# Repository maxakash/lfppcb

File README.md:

# LFP-8: 40-cell LiFePO4 33140 charger / discharger / IR tester

An open hardware tester for LiFePO4 32140/33140 cells. One **LFP-8 board**
handles **8 cells**. Five boards, JLCPCB's minimum order, test **40 cells at
once**. Each channel can

* **charge** with constant current then constant voltage: ≈ 1.0 A, CV 3.58 V,
  hardware OV latch at 3.82 V
* **discharge** at ≈ 1.07 A, with a hardware under-voltage backstop at 2.22 V
* measure **capacity** (coulomb counting, mAh/mWh) and **internal resistance**
  (pulse method, R_ohmic at 10 ms and DC-IR at 1 s) through true **4-wire
  Kelvin** connections
* read a 10 k **NTC** on every cell

Every board reports over Wi-Fi: a web dashboard and a JSON API served by its
ESP32-C3. The boards find each other, so any one of them shows all 40 cells.

| | |
|---|---|
|  |  |
| LFP-8 PCB (216 × 146 mm, 2 layers, JLCPCB assembly) | 3D-printed 8-cell module + board stand (Ender 3 S1 Pro) |

## Repository map

| Path | What |
|---|---|
| [`docs/DESIGN.md`](docs/DESIGN.md) | Architecture, circuit description, design numbers |
| [`docs/INTERFACE.md`](docs/INTERFACE.md) | Hardware ⇄ firmware contract: GPIO map, shift-register bits, thresholds, measurement formulas |
| [`docs/TEST_REPORT.md`](docs/TEST_REPORT.md) | Results of every simulation, adversarial and board-level test |
| [`docs/ORDERING_AND_ASSEMBLY.md`](docs/ORDERING_AND_ASSEMBLY.md) | How to order from JLCPCB, hand-solder parts, wiring, bring-up |
| `hardware/gen/` | **Single source of truth**: the netlist DSL (`lfp8_circuit.py`) and the generators for schematic, PCB, routing, checks and fab files |
| `hardware/kicad/` | Generated KiCad 7 project (schematic, PCB, project library) |
| `hardware/fab/` | Gerbers, drill, JLCPCB BOM + CPL, DRC report, check report |
| `sim/` | ngspice models, benches and the pytest suite (functional, adversarial, Monte Carlo, loop stability) |
| `firmware/` | ESP32-C3 Arduino firmware, web UI, REST API, IR calculator, host tests and simulator |
| `mechanical/` | OpenSCAD holder (4-cell cradles, board stand), STLs, printability checks |

## Quick start

1. **Order PCBs**: upload `hardware/fab/lfp8_gerbers.zip`, then
   `lfp8_bom_jlcpcb.csv` and `lfp8_cpl_jlcpcb.csv` for assembly. Details in
   [ORDERING_AND_ASSEMBLY.md](docs/ORDERING_AND_ASSEMBLY.md).
2. **Print the holders**: `mechanical/stl/`, 10 cradles + 5 board stands, PETG,
   no supports.
3. **Flash the firmware** through the J3 USB header:
   `make -C firmware build upload`, or open `firmware/lfp8` in the Arduino IDE
   with the ESP32 core, board *ESP32C3 Dev Module*, partition scheme
   *Minimal SPIFFS*.
4. **Power**: 5.20 V, ≥ 10 A per board. Join the board's Wi-Fi AP `LFP8-<id>` (password `lfp8admin`)
   and open `http://192.168.4.1`, or configure your Wi-Fi and use
   `http://lfp8-<id>.local`.

## Safety features (hardware, independent of firmware)

| Feature | Behaviour |
|---|---|
| CV limit | Kelvin-sensed 3.576 V (3.51–3.62 V worst case); firmware also stops at 3.60 V |
| OV latch | 3.82 V: cell isolated + charger drive killed until the cell is removed or SAFE_EN cycles |
| UV backstop | discharge stops at 2.22 V under load even if firmware hangs |
| Charge/discharge interlock | the charger is forced off while the load is on |
| Reverse cell | detected in < 50 µs; cell isolated (0.1 mA residual) whether the board is powered or not |
| Back-to-back isolation FETs | an unpowered board does not drain or back-feed the cells (81 µA residual) |
| Watchdog | a stuck or too-slow firmware loop (< 100 Hz heartbeat) shuts every channel down in 23–33 ms |
| Rail UV / OV | 4.48 V / 5.49 V |
| Board over-temperature | 70–95 °C → all channels off |
| E-STOP button | all channels off in 126 µs |
| PTC fuse per channel | 2 A hold; a board-side short trips in 0.22 s |
| TVS + reverse crowbar on the 5 V input | |

## Running the tests

```bash
./run_all_tests.sh          # ngspice suite, netlist + DRC checks, firmware tests, holder checks
QUICK=1 ./run_all_tests.sh  # shorter Monte Carlo
```

Regenerate the hardware from the DSL with `make -C hardware` (KiCad 7,
Freerouting 2.x and Java are required for routing).

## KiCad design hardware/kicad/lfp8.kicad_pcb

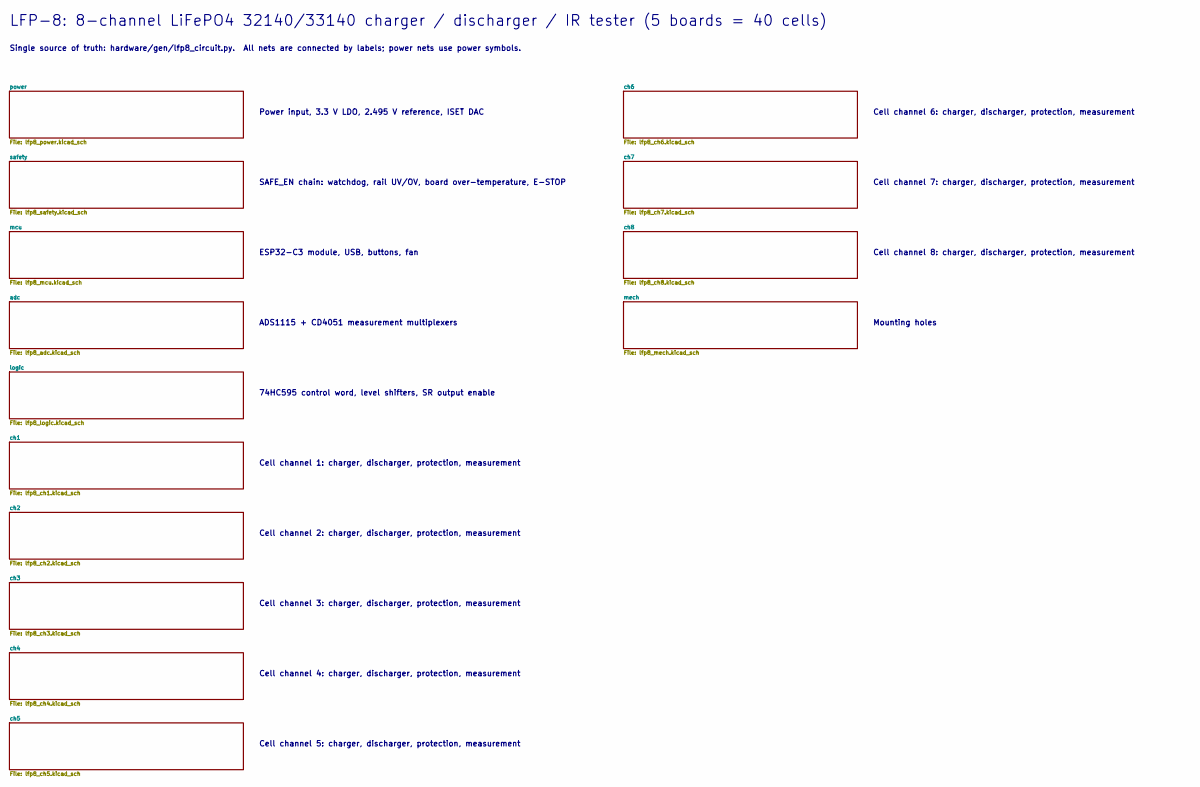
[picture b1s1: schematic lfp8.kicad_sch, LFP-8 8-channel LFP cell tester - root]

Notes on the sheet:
Power input, 3.3 V LDO, 2.495 V reference, ISET DAC
SAFE_EN chain: watchdog, rail UV/OV, board over-temperature, E-STOP
ESP32-C3 module, USB, buttons, fan
ADS1115 + CD4051 measurement multiplexers
74HC595 control word, level shifters, SR output enable
Cell channel 1: charger, discharger, protection, measurement
Cell channel 2: charger, discharger, protection, measurement
Cell channel 3: charger, discharger, protection, measurement
Cell channel 4: charger, discharger, protection, measurement
Cell channel 5: charger, discharger, protection, measurement
Cell channel 6: charger, discharger, protection, measurement
Cell channel 7: charger, discharger, protection, measurement
Cell channel 8: charger, discharger, protection, measurement
Mounting holes
LFP-8: 8-channel LiFePO4 32140/33140 charger / discharger / IR tester (5 boards = 40 cells)
Single source of truth: hardware/gen/lfp8_circuit.py. All nets are connected by labels; power nets use power symbols.

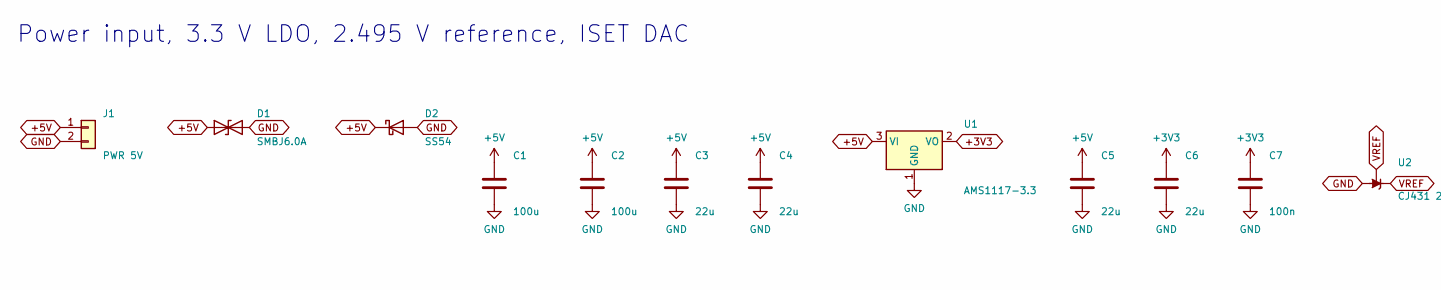
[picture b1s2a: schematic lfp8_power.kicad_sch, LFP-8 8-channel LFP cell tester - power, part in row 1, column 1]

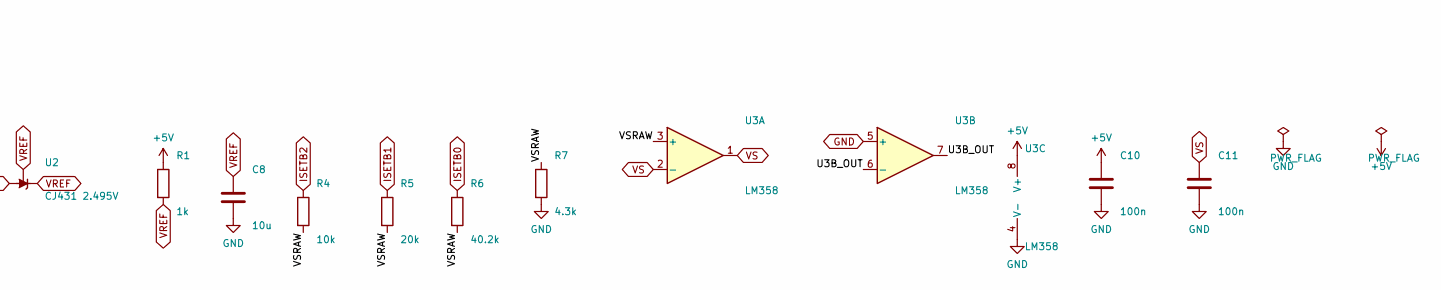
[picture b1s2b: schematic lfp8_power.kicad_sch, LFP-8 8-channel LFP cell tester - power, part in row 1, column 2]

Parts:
C1, C2: 100u; C_1206_3216Metric; LCSC C15008
C3, C4: 22u; C_1206_3216Metric; LCSC C12891
C5, C6: 22u; C_0805_2012Metric; LCSC C45783
C7, C10, C11: 100n; C_0603_1608Metric; LCSC C14663
C8: 10u; C_0805_2012Metric; LCSC C15850
D1: SMBJ6.0A; D_SMB; MPN SMBJ6.0A; LCSC C19077560
D2: SS54; D_SMA; MPN SS54; LCSC C22452
J1: PWR 5V; TerminalBlock_bornier-2_P5.08mm; MPN KF301-5.0-2P / 2-pin 5.08 mm 16 A termi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; JLC Hand
R1: 1k; R_0603_1608Metric; LCSC C21190
R4: 10k; R_0603_1608Metric; LCSC C25804
R5: 20k; R_0603_1608Metric; LCSC C4184
R6: 40.2k; R_0603_1608Metric; LCSC C12447
R7: 4.3k; R_0603_1608Metric; LCSC C23159
U1: AMS1117-3.3; SOT-223-3_TabPin2; MPN AMS1117-3.3; LCSC C6186
U2: CJ431 2.495V; SOT-23; MPN CJ431; LCSC C3113
U3: LM358; SOIC-8_3.9x4.9mm_P1.27mm; MPN LM358DR2G; LCSC C7950

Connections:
+3V3: C6.1, C7.1, U1.2 (VO); also elsewhere on the board
+5V: C1.1, C2.1, C3.1, C4.1, C5.1, C10.1, D1.1 (A1), D2.1 (K), J1.1, R1.1, U1.3 (VI), U3.8 (V+); also elsewhere on the board
/power/U3B_OUT: U3.6 (-), U3.7
/power/VSRAW: R4.2, R5.2, R6.2, R7.1, U3.3 (+)
GND: C1.2, C2.2, C3.2, C4.2, C5.2, C6.2, C7.2, C8.2, C10.2, C11.2, D1.2 (A2), D2.2 (A), J1.2, R7.2, U1.1 (GND), U2.3 (A), U3.4 (V-), U3.5 (+); also elsewhere on the board
ISETB0: R6.1; also elsewhere on the board
ISETB1: R5.1; also elsewhere on the board
ISETB2: R4.1; also elsewhere on the board
VREF: C8.1, R1.2, U2.1 (K), U2.2 (REF); also elsewhere on the board
VS: C11.1, U3.1, U3.2 (-); also elsewhere on the board

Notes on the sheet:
Power input, 3.3 V LDO, 2.495 V reference, ISET DAC

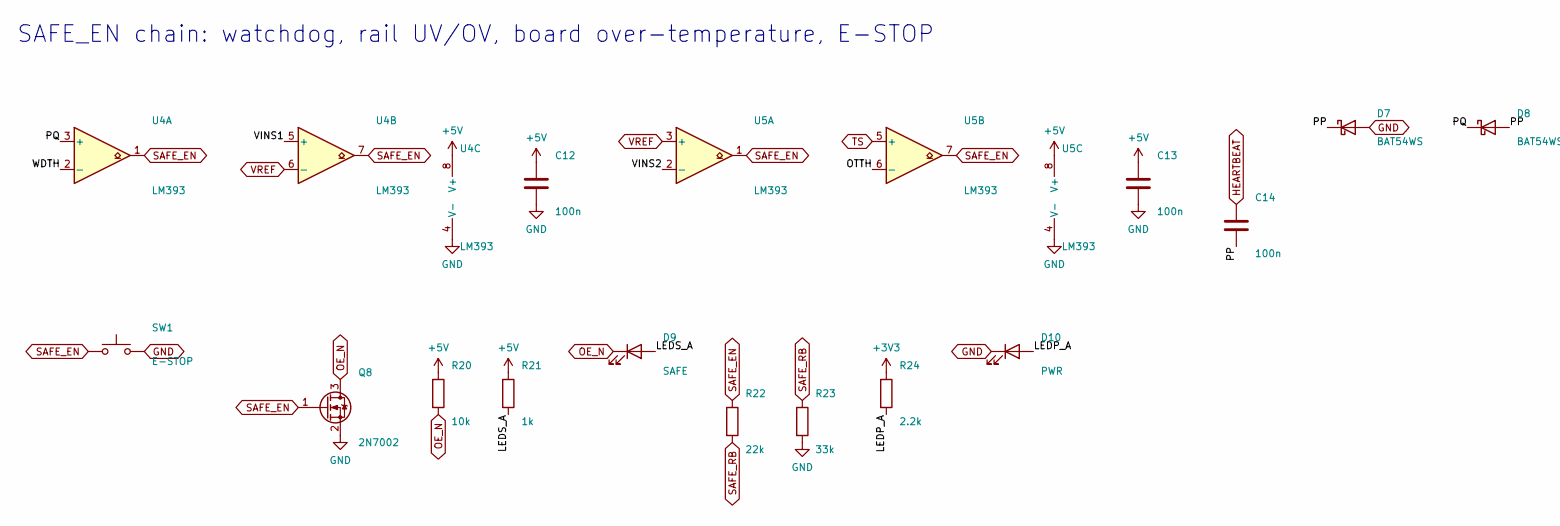
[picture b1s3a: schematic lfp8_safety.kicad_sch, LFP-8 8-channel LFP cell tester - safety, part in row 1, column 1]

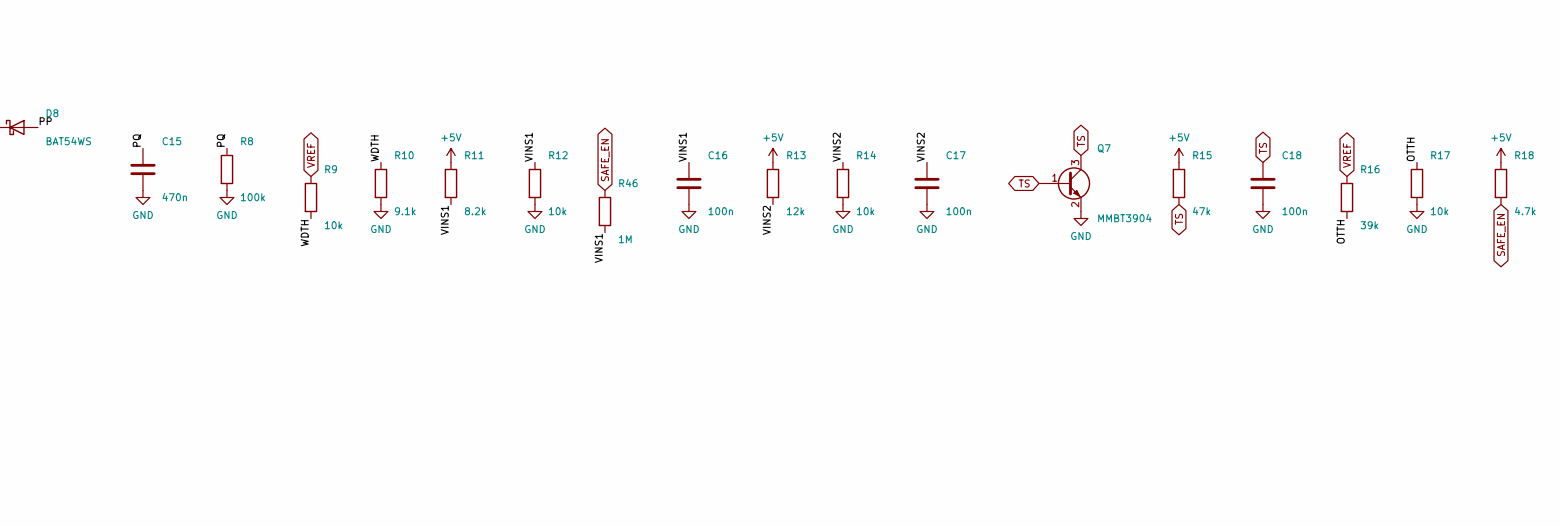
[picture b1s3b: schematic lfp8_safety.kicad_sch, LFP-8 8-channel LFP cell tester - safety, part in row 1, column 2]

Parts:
C12, C13, C14, C16, C17, C18: 100n; C_0603_1608Metric; LCSC C14663
C15: 470n; C_0603_1608Metric; LCSC C1623
D7, D8: BAT54WS; D_SOD-323; MPN BAT54WS; LCSC C7502694
D9: SAFE; LED_0805_2012Metric; MPN 0805 green; LCSC C2297
D10: PWR; LED_0603_1608Metric; MPN 0603 red; LCSC C2286
Q7: MMBT3904; SOT-23; MPN MMBT3904; LCSC C20526
Q8: 2N7002; SOT-23; MPN 2N7002; LCSC C8545
R8: 100k; R_0603_1608Metric; LCSC C25803
R9, R12, R14, R17, R20: 10k; R_0603_1608Metric; LCSC C25804
R10: 9.1k; R_0603_1608Metric; LCSC C23260
R11: 8.2k; R_0603_1608Metric; LCSC C25981
R13: 12k; R_0603_1608Metric; LCSC C22790
R15: 47k; R_0603_1608Metric; LCSC C25819
R16: 39k; R_0603_1608Metric; LCSC C23153
R18: 4.7k; R_0603_1608Metric; LCSC C23162
R21: 1k; R_0603_1608Metric; LCSC C21190
R22: 22k; R_0603_1608Metric; LCSC C31850
R23: 33k; R_0603_1608Metric; LCSC C4216
R24: 2.2k; R_0603_1608Metric; LCSC C4190
R46: 1M; R_0603_1608Metric; LCSC C22935
SW1: E-STOP; SW_SMD_5.1x5.1_4P; MPN TS-1088 type 5.1x5.1; LCSC C318884
U4, U5: LM393; SOIC-8_3.9x4.9mm_P1.27mm; MPN LM393DR2G; LCSC C7955

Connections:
+3V3: R24.1; also elsewhere on the board
+5V: C12.1, C13.1, R11.1, R13.1, R15.1, R18.1, R20.1, R21.1, U4.8 (V+), U5.8 (V+); also elsewhere on the board
/safety/LEDP_A: D10.2 (A), R24.2
/safety/LEDS_A: D9.2 (A), R21.2
/safety/OTTH: R16.2, R17.1, U5.6 (-)
/safety/PP: C14.2, D7.1 (K), D8.2 (A)
/safety/PQ: C15.1, D8.1 (K), R8.1, U4.3 (+)
/safety/VINS1: C16.1, R11.2, R12.1, R46.2, U4.5 (+)
/safety/VINS2: C17.1, R13.2, R14.1, U5.2 (-)
/safety/WDTH: R9.2, R10.1, U4.2 (-)
GND: C12.2, C13.2, C15.2, C16.2, C17.2, C18.2, D7.2 (A), D10.1 (K), Q7.2 (E), Q8.2 (S), R8.2, R10.2, R12.2, R14.2, R17.2, R23.2, SW1.2, U4.4 (V-), U5.4 (V-); also elsewhere on the board
HEARTBEAT: C14.1; also elsewhere on the board
OE_N: D9.1 (K), Q8.3 (D), R20.2; also elsewhere on the board
SAFE_EN: Q8.1 (G), R18.2, R22.1, R46.1, SW1.1, U4.1, U4.7, U5.1, U5.7; also elsewhere on the board
SAFE_RB: R22.2, R23.1; also elsewhere on the board
TS: C18.1, Q7.1 (B), Q7.3 (C), R15.2, U5.5 (+); also elsewhere on the board
VREF: R9.1, R16.1, U4.6 (-), U5.3 (+); also elsewhere on the board

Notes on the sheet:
SAFE_EN chain: watchdog, rail UV/OV, board over-temperature, E-STOP

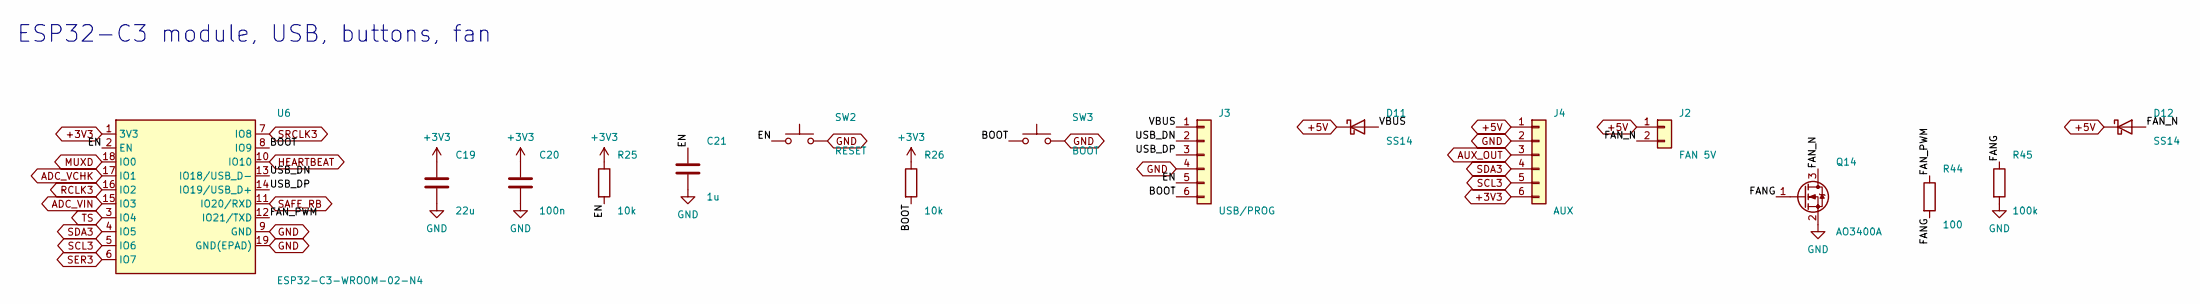
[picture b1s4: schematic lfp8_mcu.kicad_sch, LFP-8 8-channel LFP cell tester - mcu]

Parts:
C19: 22u; C_0805_2012Metric; LCSC C45783
C20: 100n; C_0603_1608Metric; LCSC C14663
C21: 1u; C_0603_1608Metric; LCSC C15849
D11, D12: SS14; D_SMA; MPN SS14; LCSC C2480
J2: FAN 5V; PinHeader_1x02_P2.54mm_Vertical; MPN 2.54 mm header; JLC Hand
J3: USB/PROG; PinHeader_1x06_P2.54mm_Vertical; MPN 2.54 mm header; JLC Hand
J4: AUX; PinHeader_1x06_P2.54mm_Vertical; MPN 2.54 mm header; JLC Hand
Q14: AO3400A; SOT-23; MPN AO3400A; LCSC C20917
R25, R26: 10k; R_0603_1608Metric; LCSC C25804
R44: 100; R_0603_1608Metric; LCSC C22775
R45: 100k; R_0603_1608Metric; LCSC C25803
SW2: RESET; SW_SMD_5.1x5.1_4P; MPN TS-1088 type 5.1x5.1; LCSC C318884
SW3: BOOT; SW_SMD_5.1x5.1_4P; MPN TS-1088 type 5.1x5.1; LCSC C318884
U6: ESP32-C3-WROOM-02-N4; ESP32-C3-WROOM-02; MPN ESP32-C3-WROOM-02-N4; LCSC C2934560

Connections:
+3V3: C19.1, C20.1, J4.6, R25.1, R26.1, U6.1 (3V3); also elsewhere on the board
+5V: D11.1 (K), D12.1 (K), J2.1, J4.1; also elsewhere on the board
/mcu/BOOT: J3.6, R26.2, SW3.1, U6.8 (IO9)
/mcu/EN: C21.1, J3.5, R25.2, SW2.1, U6.2 (EN)
/mcu/FANG: Q14.1 (G), R44.2, R45.1
/mcu/FAN_N: D12.2 (A), J2.2, Q14.3 (D)
/mcu/FAN_PWM: R44.1, U6.12 (IO21/TXD)
/mcu/USB_DN: J3.2, U6.13 (IO18/USB_D-)
/mcu/USB_DP: J3.3, U6.14 (IO19/USB_D+)
/mcu/VBUS: D11.2 (A), J3.1
ADC_VCHK: U6.17 (IO1); also elsewhere on the board
ADC_VIN: U6.15 (IO3); also elsewhere on the board
AUX_OUT: J4.3; also elsewhere on the board
GND: C19.2, C20.2, C21.2, J3.4, J4.2, Q14.2 (S), R45.2, SW2.2, SW3.2, U6.9 (GND), U6.19 (GND(EPAD)); also elsewhere on the board
HEARTBEAT: U6.10 (IO10); also elsewhere on the board
MUXD: U6.18 (IO0); also elsewhere on the board
RCLK3: U6.16 (IO2); also elsewhere on the board
SAFE_RB: U6.11 (IO20/RXD); also elsewhere on the board
SCL3: J4.5, U6.5 (IO6); also elsewhere on the board
SDA3: J4.4, U6.4 (IO5); also elsewhere on the board
SER3: U6.6 (IO7); also elsewhere on the board
SRCLK3: U6.7 (IO8); also elsewhere on the board
TS: U6.3 (IO4); also elsewhere on the board

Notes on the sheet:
ESP32-C3 module, USB, buttons, fan

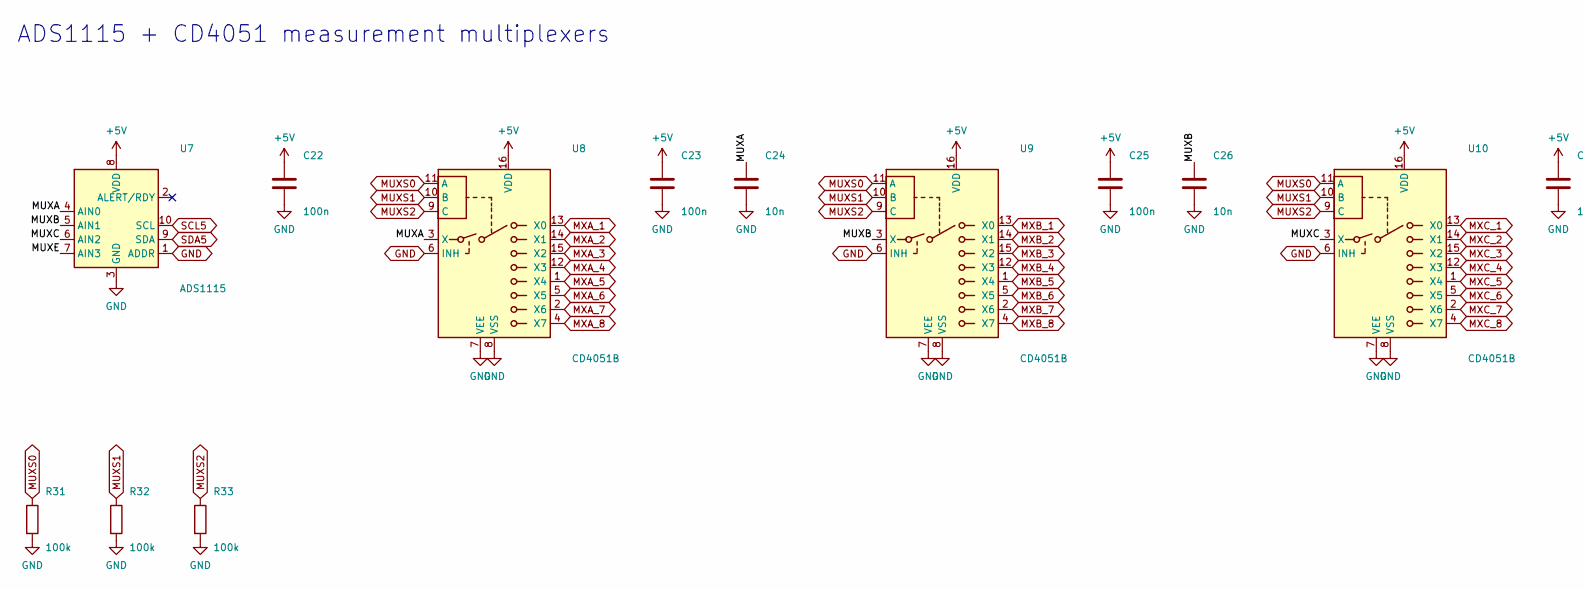
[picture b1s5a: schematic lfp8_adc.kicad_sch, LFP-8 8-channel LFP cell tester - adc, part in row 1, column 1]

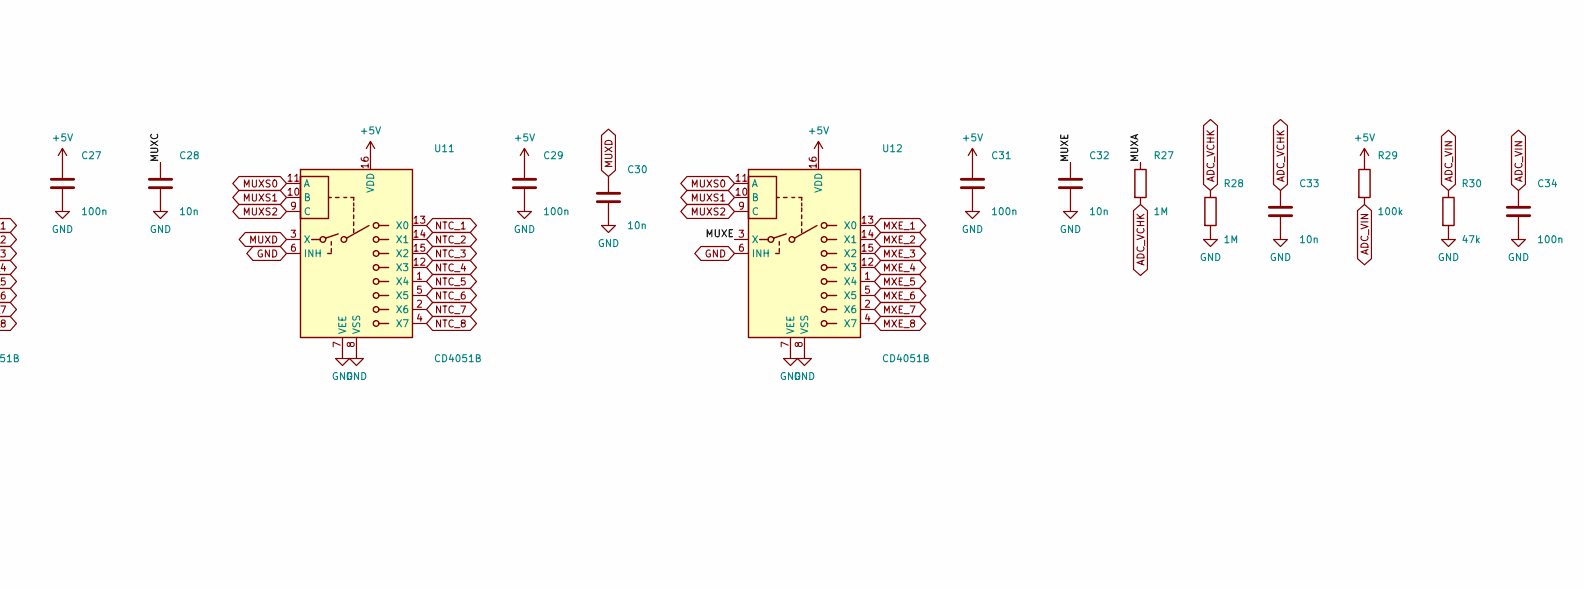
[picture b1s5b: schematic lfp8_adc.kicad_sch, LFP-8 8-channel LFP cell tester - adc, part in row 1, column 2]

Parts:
C22, C23, C25, C27, C29, C31, C34: 100n; C_0603_1608Metric; LCSC C14663
C24, C26, C28, C30, C32, C33: 10n; C_0603_1608Metric; LCSC C57112
R27, R28: 1M; R_0603_1608Metric; LCSC C22935
R29, R31, R32, R33: 100k; R_0603_1608Metric; LCSC C25803
R30: 47k; R_0603_1608Metric; LCSC C25819
U7: ADS1115; TSSOP-10_3x3mm_P0.5mm; MPN ADS1115IDGSR; LCSC C37593
U8, U9, U10, U11, U12: CD4051B; SOIC-16_3.9x9.9mm_P1.27mm; MPN CD4051BM96; LCSC C21379

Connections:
+5V: C22.1, C23.1, C25.1, C27.1, C29.1, C31.1, R29.1, U7.8 (VDD), U8.16 (VDD), U9.16 (VDD), U10.16 (VDD), U11.16 (VDD), U12.16 (VDD); also elsewhere on the board
/adc/MUXA: C24.1, R27.1, U7.4 (AIN0), U8.3 (X)
/adc/MUXB: C26.1, U7.5 (AIN1), U9.3 (X)
/adc/MUXC: C28.1, U7.6 (AIN2), U10.3 (X)
/adc/MUXE: C32.1, U7.7 (AIN3), U12.3 (X)
ADC_VCHK: C33.1, R27.2, R28.1; also elsewhere on the board
ADC_VIN: C34.1, R29.2, R30.1; also elsewhere on the board
GND: C22.2, C23.2, C24.2, C25.2, C26.2, C27.2, C28.2, C29.2, C30.2, C31.2, C32.2, C33.2, C34.2, R28.2, R30.2, R31.2, R32.2, R33.2, U7.1 (ADDR), U7.3 (GND), U8.6 (INH), U8.7 (VEE), U8.8 (VSS), U9.6 (INH), U9.7 (VEE), U9.8 (VSS), U10.6 (INH), U10.7 (VEE), U10.8 (VSS), U11.6 (INH), U11.7 (VEE), U11.8 (VSS), U12.6 (INH), U12.7 (VEE), U12.8 (VSS); also elsewhere on the board
MUXD: C30.1, U11.3 (X); also elsewhere on the board
MUXS0: R31.1, U8.11 (A), U9.11 (A), U10.11 (A), U11.11 (A), U12.11 (A); also elsewhere on the board
MUXS1: R32.1, U8.10 (B), U9.10 (B), U10.10 (B), U11.10 (B), U12.10 (B); also elsewhere on the board
MUXS2: R33.1, U8.9 (C), U9.9 (C), U10.9 (C), U11.9 (C), U12.9 (C); also elsewhere on the board
MXA_1: U8.13 (X0); also elsewhere on the board
MXA_2: U8.14 (X1); also elsewhere on the board
MXA_3: U8.15 (X2); also elsewhere on the board
MXA_4: U8.12 (X3); also elsewhere on the board
MXA_5: U8.1 (X4); also elsewhere on the board
MXA_6: U8.5 (X5); also elsewhere on the board
MXA_7: U8.2 (X6); also elsewhere on the board
MXA_8: U8.4 (X7); also elsewhere on the board
MXB_1: U9.13 (X0); also elsewhere on the board
MXB_2: U9.14 (X1); also elsewhere on the board
MXB_3: U9.15 (X2); also elsewhere on the board
MXB_4: U9.12 (X3); also elsewhere on the board
MXB_5: U9.1 (X4); also elsewhere on the board
MXB_6: U9.5 (X5); also elsewhere on the board
MXB_7: U9.2 (X6); also elsewhere on the board
MXB_8: U9.4 (X7); also elsewhere on the board
MXC_1: U10.13 (X0); also elsewhere on the board
MXC_2: U10.14 (X1); also elsewhere on the board
MXC_3: U10.15 (X2); also elsewhere on the board
MXC_4: U10.12 (X3); also elsewhere on the board
MXC_5: U10.1 (X4); also elsewhere on the board
MXC_6: U10.5 (X5); also elsewhere on the board
MXC_7: U10.2 (X6); also elsewhere on the board
MXC_8: U10.4 (X7); also elsewhere on the board
MXE_1: U12.13 (X0); also elsewhere on the board
MXE_2: U12.14 (X1); also elsewhere on the board
MXE_3: U12.15 (X2); also elsewhere on the board
MXE_4: U12.12 (X3); also elsewhere on the board
MXE_5: U12.1 (X4); also elsewhere on the board
MXE_6: U12.5 (X5); also elsewhere on the board
MXE_7: U12.2 (X6); also elsewhere on the board
MXE_8: U12.4 (X7); also elsewhere on the board
NTC_1: U11.13 (X0); also elsewhere on the board
NTC_2: U11.14 (X1); also elsewhere on the board
NTC_3: U11.15 (X2); also elsewhere on the board
NTC_4: U11.12 (X3); also elsewhere on the board
NTC_5: U11.1 (X4); also elsewhere on the board
NTC_6: U11.5 (X5); also elsewhere on the board
NTC_7: U11.2 (X6); also elsewhere on the board
NTC_8: U11.4 (X7); also elsewhere on the board
SCL5: U7.10 (SCL); also elsewhere on the board
SDA5: U7.9 (SDA); also elsewhere on the board

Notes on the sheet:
ADS1115 + CD4051 measurement multiplexers

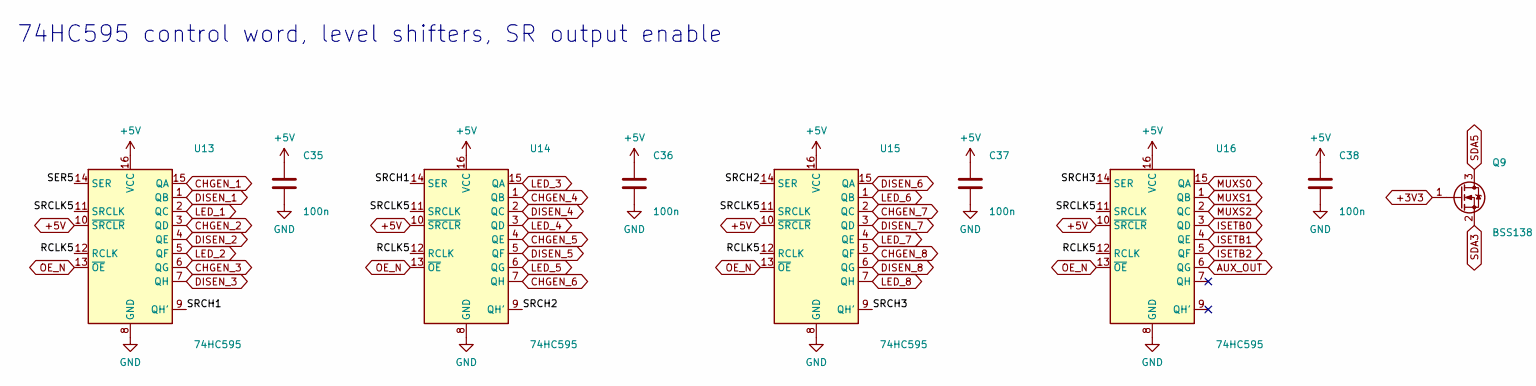
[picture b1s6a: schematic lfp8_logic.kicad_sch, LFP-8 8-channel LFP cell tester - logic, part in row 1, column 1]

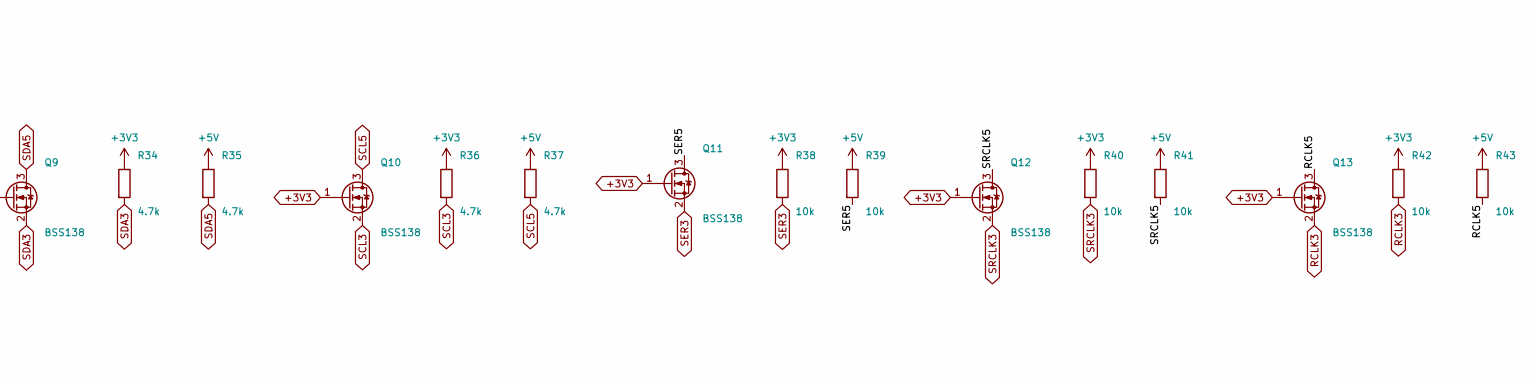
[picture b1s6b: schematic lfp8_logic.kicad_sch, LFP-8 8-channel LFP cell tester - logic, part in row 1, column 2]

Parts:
C35, C36, C37, C38: 100n; C_0603_1608Metric; LCSC C14663
Q9, Q10, Q11, Q12, Q13: BSS138; SOT-23; MPN BSS138; LCSC C7420339
R34, R35, R36, R37: 4.7k; R_0603_1608Metric; LCSC C23162
R38, R39, R40, R41, R42, R43: 10k; R_0603_1608Metric; LCSC C25804
U13, U14, U15, U16: 74HC595; SOIC-16_3.9x9.9mm_P1.27mm; MPN 74HC595D,118; LCSC C5947

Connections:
+3V3: Q9.1 (G), Q10.1 (G), Q11.1 (G), Q12.1 (G), Q13.1 (G), R34.1, R36.1, R38.1, R40.1, R42.1; also elsewhere on the board
+5V: C35.1, C36.1, C37.1, C38.1, R35.1, R37.1, R39.1, R41.1, R43.1, U13.10 (~SRCLR), U13.16 (VCC), U14.10 (~SRCLR), U14.16 (VCC), U15.10 (~SRCLR), U15.16 (VCC), U16.10 (~SRCLR), U16.16 (VCC); also elsewhere on the board
/logic/RCLK5: Q13.3 (D), R43.2, U13.12 (RCLK), U14.12 (RCLK), U15.12 (RCLK), U16.12 (RCLK)
/logic/SER5: Q11.3 (D), R39.2, U13.14 (SER)
/logic/SRCH1: U13.9 (QH'), U14.14 (SER)
/logic/SRCH2: U14.9 (QH'), U15.14 (SER)
/logic/SRCH3: U15.9 (QH'), U16.14 (SER)
/logic/SRCLK5: Q12.3 (D), R41.2, U13.11 (SRCLK), U14.11 (SRCLK), U15.11 (SRCLK), U16.11 (SRCLK)
AUX_OUT: U16.6 (QG); also elsewhere on the board
CHGEN_1: U13.15 (QA); also elsewhere on the board
CHGEN_2: U13.3 (QD); also elsewhere on the board
CHGEN_3: U13.6 (QG); also elsewhere on the board
CHGEN_4: U14.1 (QB); also elsewhere on the board
CHGEN_5: U14.4 (QE); also elsewhere on the board
CHGEN_6: U14.7 (QH); also elsewhere on the board
CHGEN_7: U15.2 (QC); also elsewhere on the board
CHGEN_8: U15.5 (QF); also elsewhere on the board
DISEN_1: U13.1 (QB); also elsewhere on the board
DISEN_2: U13.4 (QE); also elsewhere on the board
DISEN_3: U13.7 (QH); also elsewhere on the board
DISEN_4: U14.2 (QC); also elsewhere on the board
DISEN_5: U14.5 (QF); also elsewhere on the board
DISEN_6: U15.15 (QA); also elsewhere on the board
DISEN_7: U15.3 (QD); also elsewhere on the board
DISEN_8: U15.6 (QG); also elsewhere on the board
GND: C35.2, C36.2, C37.2, C38.2, U13.8 (GND), U14.8 (GND), U15.8 (GND), U16.8 (GND); also elsewhere on the board
ISETB0: U16.3 (QD); also elsewhere on the board
ISETB1: U16.4 (QE); also elsewhere on the board
ISETB2: U16.5 (QF); also elsewhere on the board
LED_1: U13.2 (QC); also elsewhere on the board
LED_2: U13.5 (QF); also elsewhere on the board
LED_3: U14.15 (QA); also elsewhere on the board
LED_4: U14.3 (QD); also elsewhere on the board
LED_5: U14.6 (QG); also elsewhere on the board
LED_6: U15.1 (QB); also elsewhere on the board
LED_7: U15.4 (QE); also elsewhere on the board
LED_8: U15.7 (QH); also elsewhere on the board
MUXS0: U16.15 (QA); also elsewhere on the board
MUXS1: U16.1 (QB); also elsewhere on the board
MUXS2: U16.2 (QC); also elsewhere on the board
OE_N: U13.13 (~OE), U14.13 (~OE), U15.13 (~OE), U16.13 (~OE); also elsewhere on the board
RCLK3: Q13.2 (S), R42.2; also elsewhere on the board
SCL3: Q10.2 (S), R36.2; also elsewhere on the board
SCL5: Q10.3 (D), R37.2; also elsewhere on the board
SDA3: Q9.2 (S), R34.2; also elsewhere on the board
SDA5: Q9.3 (D), R35.2; also elsewhere on the board
SER3: Q11.2 (S), R38.2; also elsewhere on the board
SRCLK3: Q12.2 (S), R40.2; also elsewhere on the board

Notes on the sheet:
74HC595 control word, level shifters, SR output enable

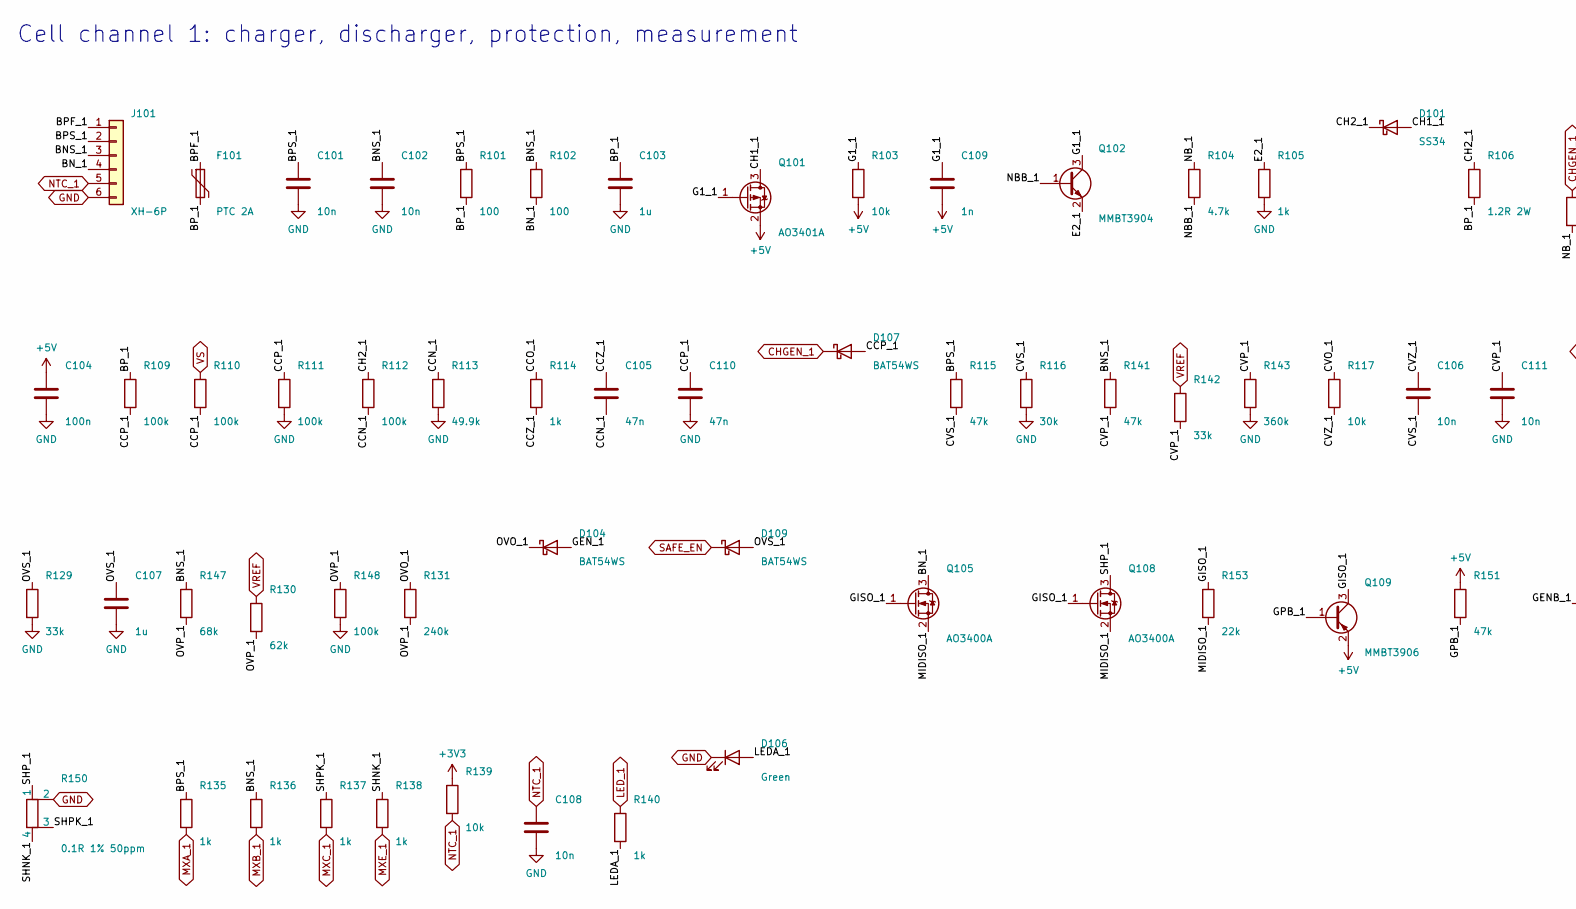
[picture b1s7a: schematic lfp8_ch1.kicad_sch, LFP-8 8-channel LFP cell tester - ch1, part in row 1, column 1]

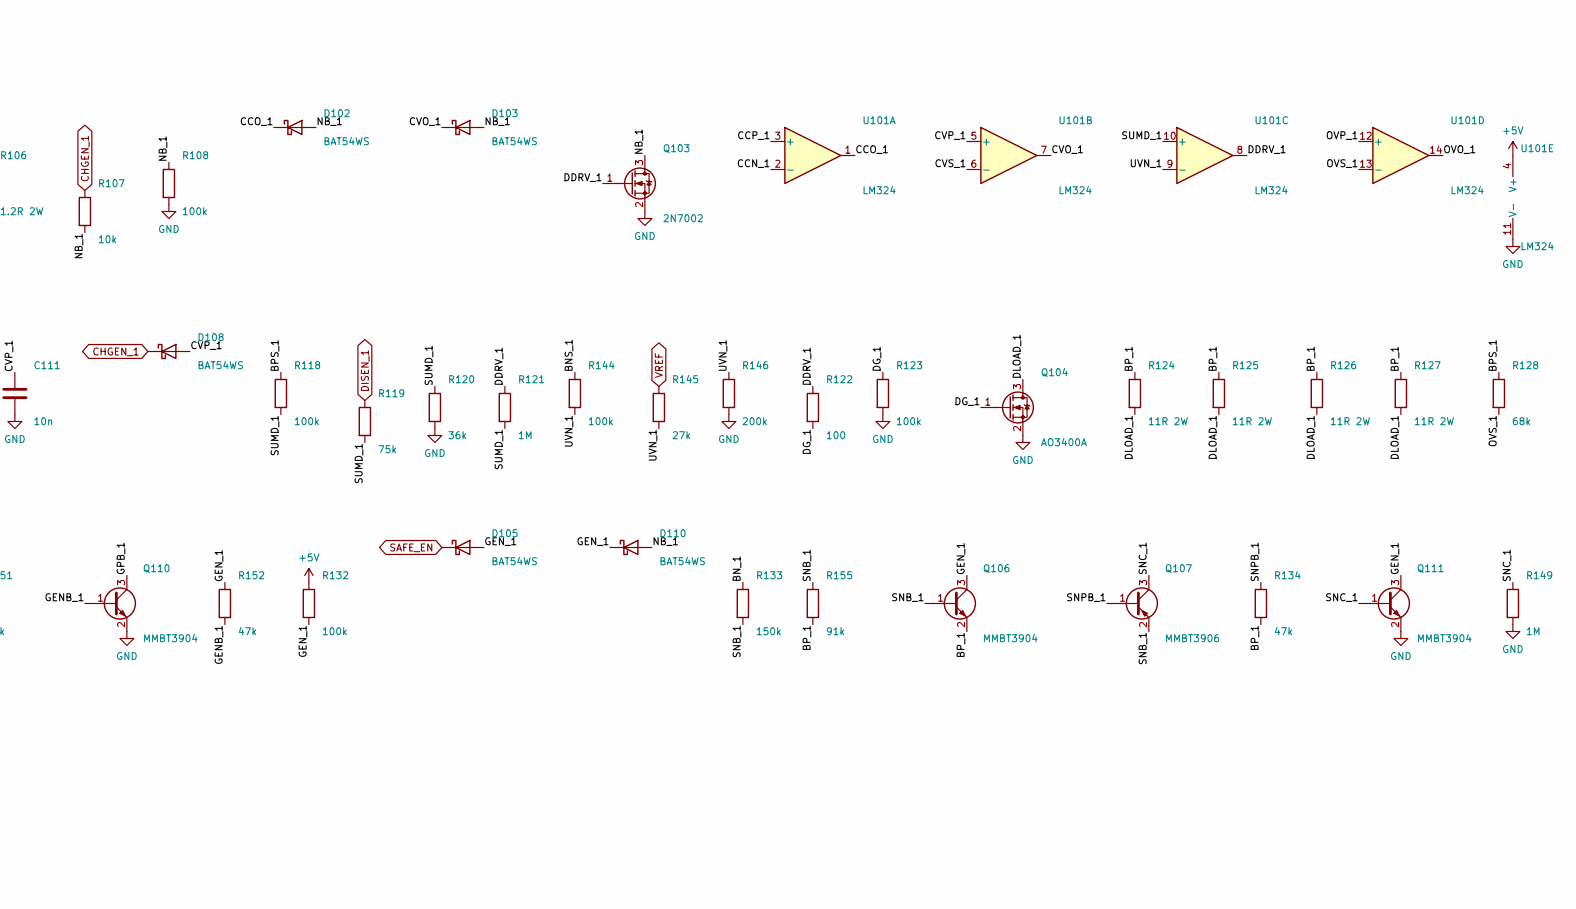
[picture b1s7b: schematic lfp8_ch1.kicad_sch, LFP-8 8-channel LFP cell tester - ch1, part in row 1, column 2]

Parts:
C101, C102, C106, C108, C111: 10n; C_0603_1608Metric; LCSC C57112
C103, C107: 1u; C_0603_1608Metric; LCSC C15849
C104: 100n; C_0603_1608Metric; LCSC C14663
C105, C110: 47n; C_0603_1608Metric; LCSC C1622
C109: 1n; C_0603_1608Metric; LCSC C1588
D101: SS34; D_SMA; MPN SS34; LCSC C8678
D102, D103, D104, D105, D107, D108, D109, D110: BAT54WS; D_SOD-323; MPN BAT54WS; LCSC C7502694
D106: Green; LED_0805_2012Metric; MPN 0805 green; LCSC C2297
F101: PTC 2A; Fuse_1812_4532Metric; MPN 1812L200/30GR; LCSC C18198342
J101: XH-6P; JST_XH_B6B-XH-A_1x06_P2.50mm_Vertical; MPN JST B6B-XH-A (or clone); JLC Hand
Q101: AO3401A; SOT-23; MPN AO3401A; LCSC C15127
Q102, Q106, Q110, Q111: MMBT3904; SOT-23; MPN MMBT3904; LCSC C20526
Q103: 2N7002; SOT-23; MPN 2N7002; LCSC C8545
Q104, Q105, Q108: AO3400A; SOT-23; MPN AO3400A; LCSC C20917
Q107, Q109: MMBT3906; SOT-23; MPN MMBT3906; LCSC C7420354
R101, R102, R122: 100; R_0603_1608Metric; LCSC C22775
R103, R107, R117, R139: 10k; R_0603_1608Metric; LCSC C25804
R104: 4.7k; R_0603_1608Metric; LCSC C23162
R105, R114, R135, R136, R137, R138, R140: 1k; R_0603_1608Metric; LCSC C21190
R106: 1.2R 2W; R_2512_6332Metric; MPN FRP2512F1R20TS; LCSC C7468247
R108, R109, R110, R111, R112, R118, R123, R132, R144, R148: 100k; R_0603_1608Metric; LCSC C25803
R113: 49.9k; R_0603_1608Metric; LCSC C23184
R115, R134, R141, R151, R152: 47k; R_0603_1608Metric; LCSC C25819
R116: 30k; R_0603_1608Metric; LCSC C22984
R119: 75k; R_0603_1608Metric; LCSC C23242
R120: 36k; R_0603_1608Metric; LCSC C23147
R121, R149: 1M; R_0603_1608Metric; LCSC C22935
R124, R125, R126, R127: 11R 2W; R_2512_6332Metric; MPN FRP2512F11R0TS; LCSC C7468192
R128, R147: 68k; R_0603_1608Metric; LCSC C23231
R129, R142: 33k; R_0603_1608Metric; LCSC C4216
R130: 62k; R_0603_1608Metric; LCSC C23221
R131: 240k; R_0603_1608Metric; LCSC C4197
R133: 150k; R_0603_1608Metric; LCSC C22807
R143: 360k; R_0603_1608Metric; LCSC C23146
R145: 27k; R_0603_1608Metric; LCSC C22967
R146: 200k; R_0603_1608Metric; LCSC C25811
R150: 0.1R 1% 50ppm; R_2512_Kelvin; MPN FRM252WFR100TN; LCSC C7420048
R153: 22k; R_0603_1608Metric; LCSC C31850
R155: 91k; R_0603_1608Metric; LCSC C23265
U101: LM324; SOIC-14_3.9x8.7mm_P1.27mm; MPN LM324DT; LCSC C71035

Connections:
+3V3: R139.1; also elsewhere on the board
+5V: C104.1, C109.2, Q101.2 (S), Q109.2 (E), R103.2, R132.1, R151.1, U101.4 (V+); also elsewhere on the board
/ch1/BNS_1: C102.1, J101.3, R102.1, R136.1, R141.1, R144.1, R147.1
/ch1/BN_1: J101.4, Q105.3 (D), R102.2, R133.1
/ch1/BPF_1: F101.1, J101.1
/ch1/BPS_1: C101.1, J101.2, R101.1, R115.1, R118.1, R128.1, R135.1
/ch1/BP_1: C103.1, F101.2, Q106.2 (E), R101.2, R106.2, R109.1, R124.1, R125.1, R126.1, R127.1, R134.2, R155.2
/ch1/CCN_1: C105.2, R112.2, R113.1, U101.2 (-)
/ch1/CCO_1: D102.1 (K), R114.1, U101.1
/ch1/CCP_1: C110.1, D107.2 (A), R109.2, R110.2, R111.1, U101.3 (+)
/ch1/CCZ_1: C105.1, R114.2
/ch1/CH1_1: D101.2 (A), Q101.3 (D)
/ch1/CH2_1: D101.1 (K), R106.1, R112.1
/ch1/CVO_1: D103.1 (K), R117.1, U101.7
/ch1/CVP_1: C111.1, D108.2 (A), R141.2, R142.2, R143.1, U101.5 (+)
/ch1/CVS_1: C106.2, R115.2, R116.1, U101.6 (-)
/ch1/CVZ_1: C106.1, R117.2
/ch1/DDRV_1: Q103.1 (G), R121.1, R122.1, U101.8
/ch1/DG_1: Q104.1 (G), R122.2, R123.1
/ch1/DLOAD_1: Q104.3 (D), R124.2, R125.2, R126.2, R127.2
/ch1/E2_1: Q102.2 (E), R105.1
/ch1/G1_1: C109.1, Q101.1 (G), Q102.3 (C), R103.1
/ch1/GENB_1: Q110.1 (B), R152.2
/ch1/GEN_1: D104.2 (A), D105.2 (A), D110.1 (K), Q106.3 (C), Q111.3 (C), R132.2, R152.1
/ch1/GISO_1: Q105.1 (G), Q108.1 (G), Q109.3 (C), R153.1
/ch1/GPB_1: Q109.1 (B), Q110.3 (C), R151.2
/ch1/LEDA_1: D106.2 (A), R140.2
/ch1/MIDISO_1: Q105.2 (S), Q108.2 (S), R153.2
/ch1/NBB_1: Q102.1 (B), R104.2
/ch1/NB_1: D102.2 (A), D103.2 (A), D110.2 (A), Q103.3 (D), R104.1, R107.2, R108.1
/ch1/OVO_1: D104.1 (K), R131.1, U101.14
/ch1/OVP_1: R130.2, R131.2, R147.2, R148.1, U101.12 (+)
/ch1/OVS_1: C107.1, D109.2 (A), R128.2, R129.1, U101.13 (-)
/ch1/SHNK_1: R138.1, R150.4
/ch1/SHPK_1: R137.1, R150.3
/ch1/SHP_1: Q108.3 (D), R150.1
/ch1/SNB_1: Q106.1 (B), Q107.2 (E), R133.2, R155.1
/ch1/SNC_1: Q107.3 (C), Q111.1 (B), R149.1
/ch1/SNPB_1: Q107.1 (B), R134.1
/ch1/SUMD_1: R118.2, R119.2, R120.1, R121.2, U101.10 (+)
/ch1/UVN_1: R144.2, R145.2, R146.1, U101.9 (-)
CHGEN_1: D107.1 (K), D108.1 (K), R107.1; also elsewhere on the board
DISEN_1: R119.1; also elsewhere on the board
GND: C101.2, C102.2, C103.2, C104.2, C107.2, C108.2, C110.2, C111.2, D106.1 (K), J101.6, Q103.2 (S), Q104.2 (S), Q110.2 (E), Q111.2 (E), R105.2, R108.2, R111.2, R113.2, R116.2, R120.2, R123.2, R129.2, R143.2, R146.2, R148.2, R149.2, R150.2, U101.11 (V-); also elsewhere on the board
LED_1: R140.1; also elsewhere on the board
MXA_1: R135.2; also elsewhere on the board
MXB_1: R136.2; also elsewhere on the board
MXC_1: R137.2; also elsewhere on the board
MXE_1: R138.2; also elsewhere on the board
NTC_1: C108.1, J101.5, R139.2; also elsewhere on the board
SAFE_EN: D105.1 (K), D109.1 (K); also elsewhere on the board
VREF: R130.1, R142.1, R145.1; also elsewhere on the board
VS: R110.1; also elsewhere on the board

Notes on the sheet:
Cell channel 1: charger, discharger, protection, measurement
